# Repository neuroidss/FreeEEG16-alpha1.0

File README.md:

# FreeEEG16-alpha1.0 TEST FAILED

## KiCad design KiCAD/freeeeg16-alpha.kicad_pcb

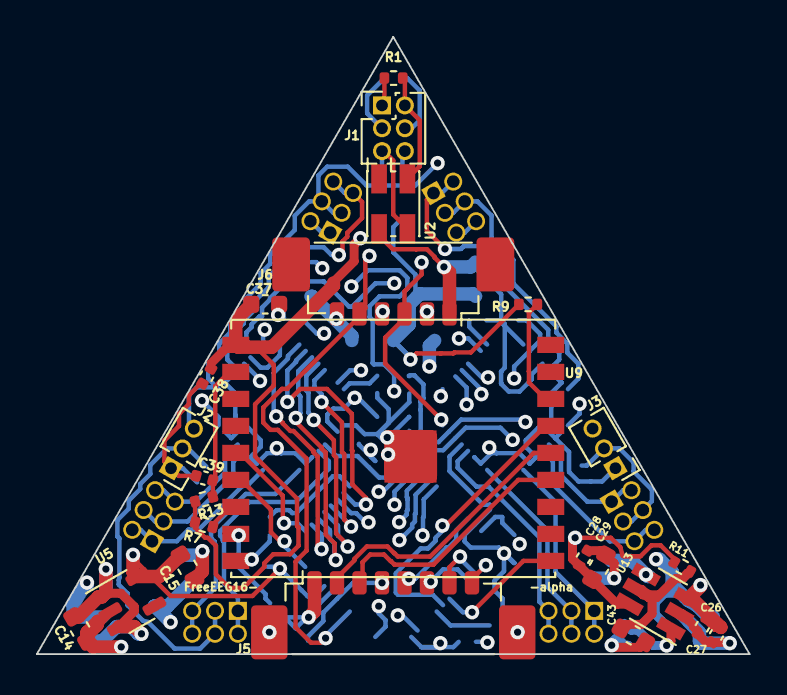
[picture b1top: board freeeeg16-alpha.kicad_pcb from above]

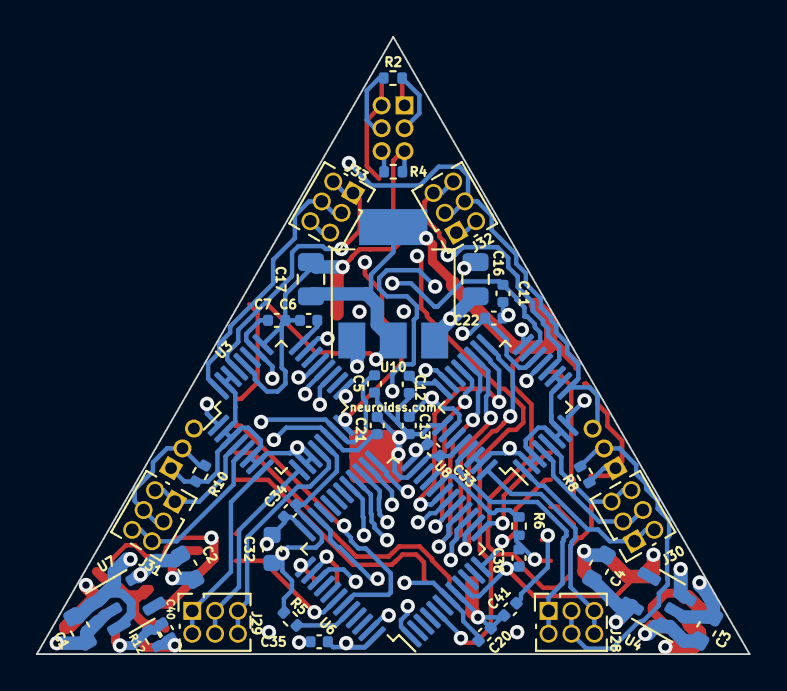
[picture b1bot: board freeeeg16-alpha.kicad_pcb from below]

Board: 4 copper layers, 39.6 x 34.3 mm, 65 parts (41 on the bottom side), 62 nets.

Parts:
C1, C2, C3, C4, C14, C15: 2.2u; C_0603_1608Metric
C5, C7, C11, C13, C27, C39: 1u; C_0402_1005Metric
C6, C12: 220n; C_0402_1005Metric
C16, C17: 22u; C_0805_2012Metric
C20, C21, C22, C26, C28, C33, C34, C35, C36, C38, C40, C41: 100n; C_0402_1005Metric
C29, C37: 10u; C_0603_1608Metric
C32: 4.7u; C_0603_1608Metric
C43: 10u DNP; C_0603_1608Metric
J1: Conn_02x03_Odd_Even; PinHeader_2x03_P1.27mm_Vertical
J2, J3: Conn_01x03; PinHeader_1x03_P1.27mm_Vertical
J5: Conn_01x08; Molex_PicoBlade_53398-0871_1x08-1MP_P1.25mm_Vertical_cut
J6: Conn_01x06; Molex_PicoBlade_53398-0671_1x06-1MP_P1.25mm_Vertical
J28, J29, J30, J31, J32, J33: Conn_02x03_Odd_Even; PinSocket_2x03_P1.27mm_Vertical
R1, R2, R4, R8, R10, R11: 0; R_0402_1005Metric
R5, R6: 4k7; R_0402_1005Metric
R7, R9, R13: 10k; R_0402_1005Metric
R12: 0 DNP; R_0402_1005Metric
U2: 8.192MHz; Oscillator_SMD_EuroQuartz_XO32-4Pin_3.2x2.5mm_HandSoldering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
U3, U8: ADS131M08IPBSR; LQFP-32_5x5mm_P0.5mm
U4, U5, U7: LP5907; SOT-23-5
U6: STM32F103CBTx; LQFP-48_7x7mm_P0.5mm
U9: ESP32-C3-WROOM-02; ESP32-C3-WROOM-02U
U10: AMS1117-3.3; SOT-223-3_TabPin2
U13: MAX6070AAUT12; SOT-23-6_Handsoldering

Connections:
3V3_1_IN: C1.1, C3.1, C14.1, C16.1, J6.6, U4.1 (IN), U4.3 (EN), U5.1 (IN), U5.3 (EN), U7.1 (IN), U7.3 (EN), U10.3 (VI)
3V3_2_GND: C1.2, C2.2, C3.2, C4.2, C5.2, C6.2, C7.2, C11.2, C12.2, C13.2, C14.2, C15.2, C16.2, C17.2, C20.1, C21.2, C22.2, C26.2, C27.2, C28.2, C29.2, C32.2, C33.2, C34.2, C35.2, C36.2, C37.2, C38.2, C39.1, C40.2, C41.1, C43.1, J2.1, J5.1, J6.1, R5.2, R6.2, R8.2, R12.2, U2.2 (GND), U3.13 (AGND), U3.25 (DGND), U3.28 (AGND), U4.2 (GND), U5.2 (GND), U6.8 (VSSA), U6.23 (VSS), U6.35 (VSS), U6.47 (VSS), U7.2 (GND), U8.13 (AGND), U8.25 (DGND), U8.28 (AGND), U9.9 (GND), U9.19 (GND), U10.1 (GND), U13.2 (GND)
3V3_5_OUT: C17.1, C37.1, C38.1, R7.2, R9.2, R13.2, U9.1 (3V3), U10.2 (VO)
/ADC1/24_CAP: C12.1, U8.24 (CAP)
/ADC2/24_CAP: C6.1, U3.24 (CAP)
/J17: J3.2, J31.3, J31.4, R10.1
/J18: J2.2, J28.3, J28.4, R8.1
/vref2/1_FILTER: C40.1, R12.1, U13.1 (FILTER)
ACC_5_VDDIO: C15.1, C32.1, C33.1, C34.1, C35.1, C36.1, J1.1, R1.1, U5.5 (OUT), U6.1 (VBAT), U6.9 (VDDA), U6.24 (VDD), U6.36 (VDD), U6.48 (VDD)
ACC_13_SCL: U6.42 (PB6), U9.10 (GPIO10)
ACC_14_SDA: U6.43 (PB7), U9.15 (GPIO3/ADC1_CH3)
ADC1_01_AIN2P: J30.1, J30.2, U8.1 (AIN2P)
ADC1_02_AIN2N: J3.1, J6.2, R10.2, U3.2 (AIN2N), U3.3 (AIN3N), U3.6 (AIN4N), U3.7 (AIN5N), U3.10 (AIN6N), U3.11 (AIN7N), U3.30 (AIN0N), U3.31 (AIN1N), U8.2 (AIN2N), U8.3 (AIN3N), U8.6 (AIN4N), U8.7 (AIN5N), U8.10 (AIN6N), U8.11 (AIN7N), U8.30 (AIN0N), U8.31 (AIN1N)
ADC1_04_AIN3P: J30.3, J30.4, U8.4 (AIN3P)
ADC1_05_AIN4P: J30.5, J30.6, U8.5 (AIN4P)
ADC1_08_AIN5P: J32.1, J32.2, U8.8 (AIN5P)
ADC1_09_AIN6P: J2.3, J3.3, J32.3, J32.4, U8.9 (AIN6P)
ADC1_12_AIN7P: J32.5, J32.6, U8.12 (AIN7P)
ADC1_14_REFIN: C21.1, C22.1, C28.1, C29.1, J6.4, R11.2, U3.14 (REFIN), U8.14 (REFIN), U13.6 (OUTF)
ADC1_15_AVDD: C2.1, C5.1, C11.1, C26.1, C27.1, U3.15 (AVDD), U7.5 (OUT), U8.15 (AVDD), U13.3 (EN), U13.4 (IN)
ADC1_16_SYNC/RESET: J1.4, J6.3, R2.2, U3.16 (SYNC/RESET), U8.16 (SYNC/RESET)
ADC1_17_CS: U6.14 (PA4), U8.17 (CS)
ADC1_18_DRDY: U6.19 (PB1), U8.18 (DRDY)
ADC1_19_SCLK: U6.15 (PA5), U8.19 (SCLK)
ADC1_20_DOUT: U6.16 (PA6), U8.20 (DOUT)
ADC1_21_DIN: U6.17 (PA7), U8.21 (DIN)
ADC1_23_XTAL1/CLKIN: U3.23 (XTAL1/CLKIN), U6.29 (PA8), U8.23 (XTAL1/CLKIN)
ADC1_26_DVDD: C4.1, C7.1, C13.1, U3.26 (DVDD), U4.5 (OUT), U8.26 (DVDD)
ADC1_29_AIN0P: J28.1, J28.2, U8.29 (AIN0P)
ADC1_32_AIN1P: J28.5, J28.6, U8.32 (AIN1P)
ADC2_01_AIN2P: J33.5, J33.6, U3.1 (AIN2P)
ADC2_04_AIN3P: J31.1, J31.2, U3.4 (AIN3P)
ADC2_05_AIN4P: J31.5, J31.6, U3.5 (AIN4P)
ADC2_08_AIN5P: J29.1, J29.2, U3.8 (AIN5P)
ADC2_09_AIN6P: J29.3, J29.4, U3.9 (AIN6P)
ADC2_12_AIN7P: J29.5, J29.6, U3.12 (AIN7P)
ADC2_17_CS: U3.17 (CS), U6.25 (PB12)
ADC2_19_SCLK: U3.19 (SCLK), U6.26 (PB13)
ADC2_20_DOUT: U3.20 (DOUT), U6.27 (PB14)
ADC2_21_DIN: U3.21 (DIN), U6.28 (PB15)
ADC2_29_AIN0P: J33.1, J33.2, U3.29 (AIN0P)
ADC2_32_AIN1P: J33.3, J33.4, U3.32 (AIN1P)
CRYSTAL_3_OUT: J1.5, R4.1, U2.3 (OUT)
CRYSTAL_4_Vin: J1.2, R1.2, U2.4 (Vin)
MCU_5_PDO0_RCC_OSC_IN: J1.6, J6.5, R4.2, U6.5 (PD0)
MCU_7_NRST: C20.2, J5.4, U6.7 (NRST)
MCU_12_PA2_USART2_TX: U6.12 (PA2), U9.6 (GPIO7)
MCU_13_PA3_USART2_RX: U6.13 (PA3), U9.5 (GPIO6)
MCU_18_PB0_ADC1_SYNC/RESET: J1.3, R2.1, U6.18 (PB0)
MCU_20_PB2_BOOT1: R6.1, U6.20 (PB2)
MCU_34_PA13_SYS_JTMS-SWDIO: J5.5, U6.34 (PA13)
MCU_37_PA14_SYS_JTCK-SWCLK: J5.8, U6.37 (PA14)
MCU_38_PA15_SYS_JTDI: J5.7, U6.38 (PA15)
MCU_39_PB3_SYS_JTDO-TRACESWO: J5.6, U6.39 (PB3)
MCU_44_BOOT0: R5.1, U6.44 (BOOT0)
unnamed: C43.2, R11.1, U13.5 (OUTS)
RADIO_2_EN: C39.2, R13.1, U9.2 (EN/CHIP_PU)
RADIO_7_GPIO8: R7.1, U9.7 (GPIO8)
RADIO_8_GPIO9: C41.2, U9.8 (GPIO9)
RADIO_13_GPIO18/USB_D-: J5.3, U9.13 (GPIO18/USB_D-)
RADIO_14_GPIO19/USB_D+: J5.2, U9.14 (GPIO19/USB_D+)
RADIO_16_GPIO2: R9.1, U9.16 (GPIO2/ADC1_CH2)

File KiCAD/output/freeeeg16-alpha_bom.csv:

"Id";"Designator";"Footprint";"Quantity";"Designation";"Supplier and ref";
1;"C14,C15,C3,C2,C1,C4";"C_0603_1608Metric";6;"2.2u";;;
2;"C29,C37";"C_0603_1608Metric";2;"10u";;;
3;"R13,R9,R7";"R_0402_1005Metric";3;"10k";;;
4;"C39,C27,C5,C11,C13,C7";"C_0402_1005Metric";6;"1u";;;
5;"C38,C26,C28,C36,C40,C22,C20,C35,C21,C33,C41,C34";"C_0402_1005Metric";12;"100n";;;
6;"R11,R1,R8,R4,R2,R10";"R_0402_1005Metric";6;"0";;;
7;"J1";"PinHeader_2x03_P1.27mm_Vertical";1;"Conn_02x03_Odd_Even";;;
8;"C43";"C_0603_1608Metric";1;"10u DNP";;;
9;"U5,U4,U7";"SOT-23-5";3;"LP5907";;;
10;"U13";"SOT-23-6_Handsoldering";1;"MAX6070AAUT12";;;
11;"J5";"Molex_PicoBlade_53398-0871_1x08-1MP_P1.25mm_Vertical_cut";1;"Conn_01x08";;;
12;"J6";"Molex_PicoBlade_53398-0671_1x06-1MP_P1.25mm_Vertical";1;"Conn_01x06";;;
13;"J3,J2";"PinHeader_1x03_P1.27mm_Vertical";2;"Conn_01x03";;;
14;"U2";"Oscillator_SMD_EuroQuartz_XO32-4Pin_3.2x2.5mm_HandSoldering_cut";1;"8.192MHz";;;
15;"U9";"ESP32-C3-WROOM-02U";1;"ESP32-C3-WROOM-02";;;
16;"J29,J28,J31,J32,J33,J30";"PinSocket_2x03_P1.27mm_Vertical";6;"Conn_02x03_Odd_Even";;;
17;"R6,R5";"R_0402_1005Metric";2;"4k7";;;
18;"U6";"LQFP-48_7x7mm_P0.5mm";1;"STM32F103CBTx";;;
19;"U10";"SOT-223-3_TabPin2";1;"AMS1117-3.3";;;
20;"C12,C6";"C_0402_1005Metric";2;"220n";;;
21;"U3,U8";"LQFP-32_5x5mm_P0.5mm";2;"ADS131M08IPBSR";;;
22;"C16,C17";"C_0805_2012Metric";2;"22u";;;
23;"C32";"C_0603_1608Metric";1;"4.7u";;;
24;"R12";"R_0402_1005Metric";1;"0 DNP";;;

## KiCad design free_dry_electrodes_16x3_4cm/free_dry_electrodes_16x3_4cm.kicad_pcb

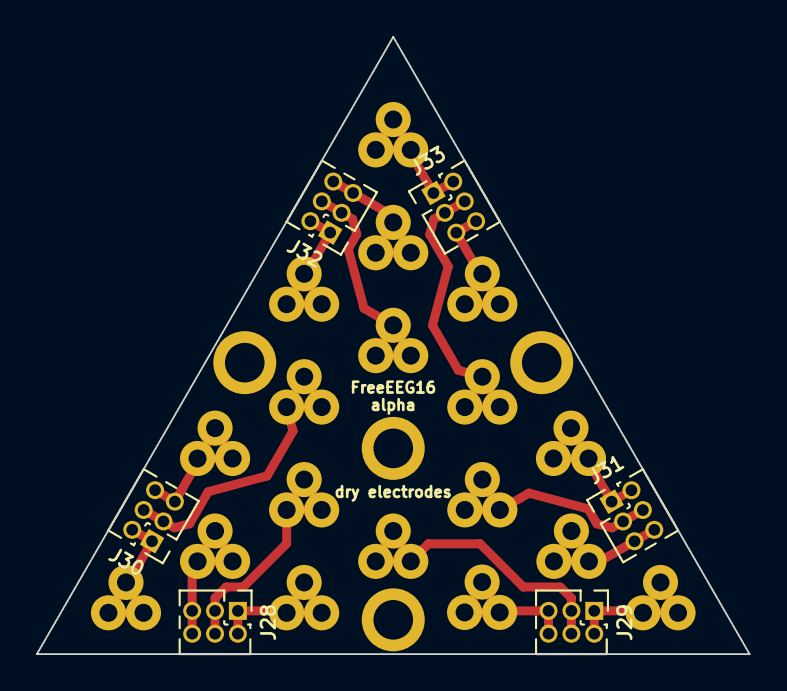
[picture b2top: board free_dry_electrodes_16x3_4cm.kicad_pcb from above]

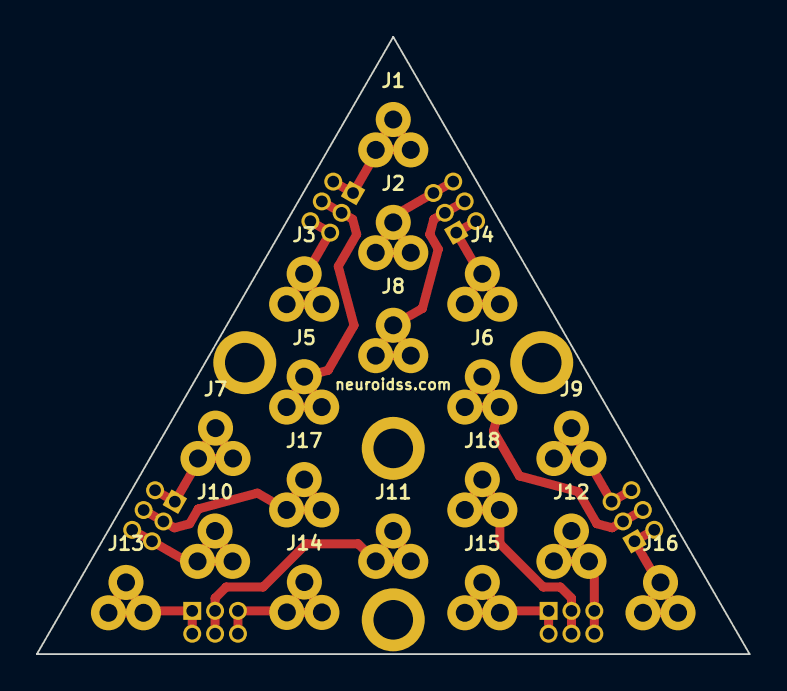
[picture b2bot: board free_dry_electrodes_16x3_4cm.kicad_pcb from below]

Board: 2 copper layers, 39.6 x 34.3 mm, 24 parts (18 on the bottom side), 18 nets.

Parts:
J1, J2, J3, J4, J5, J6, J7, J8, J9, J10, J11, J12, J13, J14, J15, J16, J17, J18: Conn_01x03; CPA_3_od4.5_d1.95_id1.0
J28, J29, J30, J31, J32, J33: Conn_02x03_Odd_Even; PinHeader_2x03_P1.27mm_Vertical

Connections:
/J1: J1.1, J1.2, J1.3, J33.1, J33.2
/J2: J2.1, J2.2, J2.3, J32.5, J32.6
/J3: J3.1, J3.2, J3.3, J33.5, J33.6
/J4: J4.1, J4.2, J4.3, J32.1, J32.2
/J5: J5.1, J5.2, J5.3, J33.3, J33.4
/J6: J6.1, J6.2, J6.3, J30.3, J30.4
/J7: J7.1, J7.2, J7.3, J31.1, J31.2
/J8: J8.1, J8.2, J8.3, J32.3, J32.4
/J9: J9.1, J9.2, J9.3, J30.5, J30.6
/J10: J10.1, J10.2, J10.3, J31.5, J31.6
/J11: J11.1, J11.2, J11.3, J29.3, J29.4
/J12: J12.1, J12.2, J12.3, J28.5, J28.6
/J13: J13.1, J13.2, J13.3, J29.1, J29.2
/J14: J14.1, J14.2, J14.3, J29.5, J29.6
/J15: J15.1, J15.2, J15.3, J28.1, J28.2
/J16: J16.1, J16.2, J16.3, J30.1, J30.2
/J17: J17.1, J17.2, J17.3, J31.3, J31.4
/J18: J18.1, J18.2, J18.3, J28.3, J28.4

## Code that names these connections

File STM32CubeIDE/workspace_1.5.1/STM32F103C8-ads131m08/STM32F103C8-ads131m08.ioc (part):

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Mcu.Name=STM32F103C(8-B)Tx
Mcu.Package=LQFP48
Mcu.UserName=STM32F103C8Tx
PA10.Mode=Asynchronous
PA10.Signal=USART1_RX
PA13.Mode=JTAG_4_pins
PA13.Signal=SYS_JTMS-SWDIO
PA14.Mode=JTAG_4_pins
PA14.Signal=SYS_JTCK-SWCLK
PA15.Mode=JTAG_4_pins
PA15.Signal=SYS_JTDI
PA2.Mode=Asynchronous
PA2.Signal=USART2_TX
PA3.Mode=Asynchronous
PA3.Signal=USART2_RX
PA4.GPIOParameters=GPIO_Speed,PinState,GPIO_Label
PA4.GPIO_Label=SPI1_NSS
PA4.GPIO_Speed=GPIO_SPEED_FREQ_HIGH
PA4.PinState=GPIO_PIN_SET
PA4.Signal=GPIO_Output
PA5.Mode=Full_Duplex_Master
PA5.Signal=SPI1_SCK
PA6.Mode=Full_Duplex_Master
PA6.Signal=SPI1_MISO
PA7.Mode=Full_Duplex_Master
PA7.Signal=SPI1_MOSI
PA8.Mode=Clock-out
PA8.Signal=RCC_MCO
PA9.Mode=Asynchronous
PA9.Signal=USART1_TX
PB0.GPIOParameters=GPIO_Label
PB0.GPIO_Label=ADC1_SYNC_RESET
PB0.Signal=GPIO_Output
PB1.GPIOParameters=GPIO_Label
PB1.GPIO_Label=ADC1_DRDY
PB1.Signal=GPXTI1
PB10.Mode=Asynchronous
PB10.Signal=USART3_TX
PB11.Mode=Asynchronous
PB11.Signal=USART3_RX
PB12.GPIOParameters=GPIO_Speed,PinState,GPIO_Label
PB12.GPIO_Label=SPI2_NSS
PB12.GPIO_Speed=GPIO_SPEED_FREQ_HIGH
PB12.PinState=GPIO_PIN_SET
PB12.Signal=GPIO_Output
PB13.Mode=Full_Duplex_Master
PB13.Signal=SPI2_SCK
PB14.Mode=Full_Duplex_Master
PB14.Signal=SPI2_MISO
PB15.Mode=Full_Duplex_Master
PB15.Signal=SPI2_MOSI
PB2.GPIOParameters=GPIO_Label
PB2.GPIO_Label=BOOT1
PB2.Signal=GPIO_Input
PB3.Mode=JTAG_4_pins
PB3.Signal=SYS_JTDO-TRACESWO
PB6.Mode=I2C
PB6.Signal=I2C1_SCL
PB7.Mode=I2C
PB7.Signal=I2C1_SDA
PD0-OSC_IN.Mode=HSE-External-Clock-Source
PD0-OSC_IN.Signal=RCC_OSC_IN
PD1-OSC_OUT.Mode=HSE-External-Clock-Source
PD1-OSC_OUT.Signal=RCC_OSC_OUT
RCC.HSEDivPLL=RCC_HSE_PREDIV_DIV2
RCC.HSE_VALUE=8192000
RCC.SYSCLKFreq_VALUE=65536000
RCC.SYSCLKSource=RCC_SYSCLKSOURCE_PLLCLK
board=custom
